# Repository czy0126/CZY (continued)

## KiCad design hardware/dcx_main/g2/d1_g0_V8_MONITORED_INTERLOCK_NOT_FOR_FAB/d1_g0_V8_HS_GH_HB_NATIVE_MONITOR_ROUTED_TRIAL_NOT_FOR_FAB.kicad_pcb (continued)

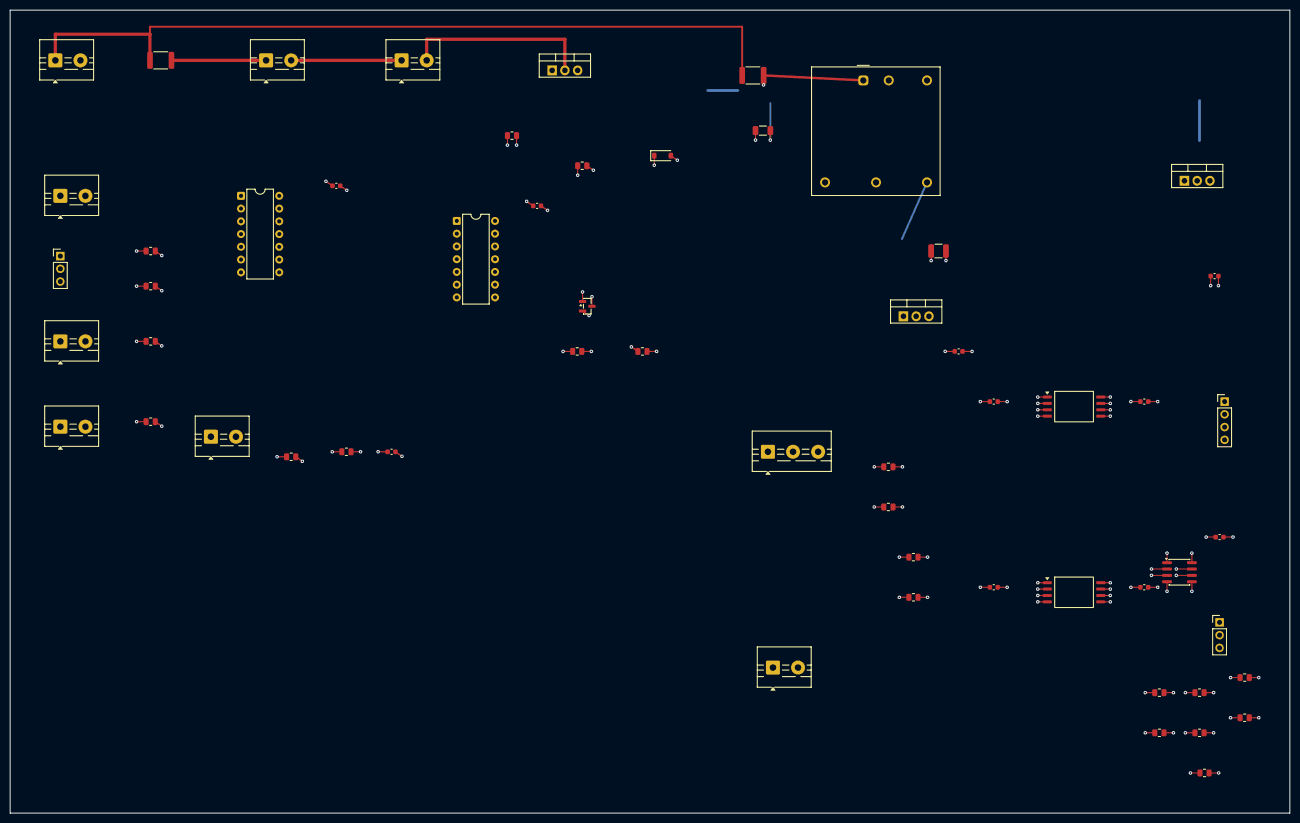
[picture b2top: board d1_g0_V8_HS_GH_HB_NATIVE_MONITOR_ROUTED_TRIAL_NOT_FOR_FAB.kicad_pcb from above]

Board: 6 copper layers, 255.0 x 160.0 mm, 58 parts (0 on the bottom side), 37 nets.

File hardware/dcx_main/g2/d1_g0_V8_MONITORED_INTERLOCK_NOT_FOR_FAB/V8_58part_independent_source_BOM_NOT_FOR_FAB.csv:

Reference,VendorOrCandidateValue,KiCadNativeFootprint,IndependentPadNetContract,NativeKiCad_DNP,AssemblyQualified,G0FabApproved
C_AND,100nF_25V,Capacitor_SMD:C_0603_1608Metric,1=VCC12;2=PGND,NO,NO,NO
C_ARM,100nF_25V_DEBOUNCE_START,Capacitor_SMD:C_0603_1608Metric,1=ARM_CLOCK;2=PGND,NO,NO,NO
C_GH_H,100nF_HS5V_LOCAL,Capacitor_SMD:C_0603_1608Metric,1=HS5V;2=HS_SW,NO,NO,NO
C_GH_L,100nF_PRI5V_LOCAL,Capacitor_SMD:C_0603_1608Metric,1=PRI5V;2=PGND,NO,NO,NO
C_HB_H,100nF_HS5V_LOCAL,Capacitor_SMD:C_0603_1608Metric,1=HS5V;2=HS_SW,NO,NO,NO
C_HB_L,100nF_PRI5V_LOCAL,Capacitor_SMD:C_0603_1608Metric,1=PRI5V;2=PGND,NO,NO,NO
C_HS5,100nF_25V_X7R,Capacitor_SMD:C_0603_1608Metric,1=HS5V;2=HS_SW,NO,NO,NO
C_HS_COMP,100nF_PRI5V_TO_PGND,Capacitor_SMD:C_0603_1608Metric,1=PRI5V;2=PGND,NO,NO,NO
C_HS_IN,1uF_100V_X7R,Capacitor_SMD:C_1206_3216Metric,1=VIN48_HS_F;2=PGND,NO,NO,NO
C_HS_OUT,22uF_25V_X7R,Capacitor_SMD:C_1210_3225Metric,1=HS_VB;2=HS_SW,NO,NO,NO
C_LATCH,100nF_25V,Capacitor_SMD:C_0603_1608Metric,1=VCC12;2=PGND,NO,NO,NO
C_PRI5,100nF_25V_X7R,Capacitor_SMD:C_0603_1608Metric,1=PRI5V;2=PGND,NO,NO,NO
D_GS,13V_ZENER_1_CATHODE_G_2_ANODE_S_DFM_REVIEW,Diode_SMD:D_SOD-123,1=MOS_GATE;2=PGND,NO,NO,NO
F_COIL,2A_SLOW_75VDC_MIN_BREAKING_I2T_UNQUALIFIED,Fuse:Fuse_1812_4532Metric,1=VIN48_AUX;2=48V_FUSED,NO,NO,NO
F_HS12,2A_SLOW_DC_BREAKING_UNQUALIFIED,Fuse:Fuse_1812_4532Metric,1=VIN48_AUX;2=VIN48_HS_F,NO,NO,NO
J_ARM,MOMENTARY_NO_MANUAL_RESTART_REQUIRED,TerminalBlock:TerminalBlock_MaiXu_MX126-5.0-02P_1x02_P5.00mm,1=VCC12;2=ARM_RAW,NO,NO,NO
J_AUX48,48V_AUX_PRE_POWER_DC_FUSED_INLET,TerminalBlock:TerminalBlock_MaiXu_MX126-5.0-02P_1x02_P5.00mm,1=VIN48_AUX;2=PGND,NO,NO,NO
J_BIAS,V6_BIAS_PRIMARY_12V_PGND,TerminalBlock:TerminalBlock_MaiXu_MX126-5.0-02P_1x02_P5.00mm,1=VCC12;2=PGND,NO,NO,NO
J_ESTOP_MON,2ND_INDEPENDENT_NC_ESTOP_CONTACT_CHANNEL_B,TerminalBlock:TerminalBlock_MaiXu_MX126-5.0-02P_1x02_P5.00mm,1=VCC12;2=ESTOP_MON_OK,NO,NO,NO
J_ESTOP_PWR,EXTERNAL_2_CONTACT_NC_ESTOP_CHANNEL_A,TerminalBlock:TerminalBlock_MaiXu_MX126-5.0-02P_1x02_P5.00mm,1=48V_FUSED;2=48V_AFTER_ESTOP,NO,NO,NO
J_GX14COIL,GX14FAC_48V_COIL_LEADS_EXTERNAL_NO_EXTRA_DIODE,TerminalBlock:TerminalBlock_MaiXu_MX126-5.0-02P_1x02_P5.00mm,1=48V_AFTER_ESTOP;2=COIL_DRAIN,NO,NO,NO
J_HEALTH,V6_UVLO_P_OK_S_OK_GND,Connector_PinHeader_2.54mm:PinHeader_1x03_P2.54mm_Vertical,1=UVLO_P_OK;2=UVLO_S_PRIMARY_OK;3=PGND,NO,NO,NO
J_HS_DIFF,GH_OUTP_GH_OUTN_HB_OUTP_HB_OUTN,Connector_PinHeader_2.54mm:PinHeader_1x04_P2.54mm_Vertical,1=GH_OUTP;2=GH_OUTN;3=HB_OUTP;4=HB_OUTN,NO,NO,NO
J_HS_FLAGS,HB_VALID_GH_OFF_PGND_DIAGNOSTICS_ONLY,Connector_PinHeader_2.54mm:PinHeader_1x03_P2.54mm_Vertical,1=HB_VALID;2=GH_GATE_OFF;3=PGND,NO,NO,NO
J_HS_FLOAT_BIAS,FLOATING_12V_HB_AND_SW_TO_DRIVER_CHECK_V5_COMPATIBILITY,TerminalBlock:TerminalBlock_MaiXu_MX126-5.0-02P_1x02_P5.00mm,1=HS_VB;2=HS_SW,NO,NO,NO
J_HS_OK,INDEPENDENT_HS_GH_SW_SENSOR_OK_MANDATORY,TerminalBlock:TerminalBlock_MaiXu_MX126-5.0-02P_1x02_P5.00mm,1=HS_OK_IN;2=PGND,NO,NO,NO
J_HS_SENSE,HIGH_SIDE_GH1_HB_AND_KELVIN_SW_FROM_ACTUAL_DRIVER,TerminalBlock:TerminalBlock_MaiXu_MX126-5.0-03P_1x03_P5.00mm,1=GH_RAW;2=HB_RAW;3=HS_SW,NO,NO,NO
Q_COIL,Infineon_IRL540NPbF_100V_36A_G1D2S3,Package_TO_SOT_THT:TO-220-3_Vertical,1=MOS_GATE;2=COIL_DRAIN;3=PGND,NO,NO,NO
Q_RESET,onsemi_MMBT3904LT1G_1B_2E_3C,Package_TO_SOT_SMD:SOT-23,1=RESET_BASE;2=PGND;3=RESET_ACTIVE,NO,NO,NO
R_ARM_DN,100k_0805_FAIL_OFF,Resistor_SMD:R_0805_2012Metric,1=ARM_RAW;2=PGND,NO,NO,NO
R_ARM_SER,4k7_0805,Resistor_SMD:R_0805_2012Metric,1=ARM_RAW;2=ARM_CLOCK,NO,NO,NO
R_ESTOP_DN,100k_0805_FAIL_OFF,Resistor_SMD:R_0805_2012Metric,1=ESTOP_MON_OK;2=PGND,NO,NO,NO
R_GATE,100R_0805,Resistor_SMD:R_0805_2012Metric,1=COIL_ENABLE;2=MOS_GATE,NO,NO,NO
R_GATE_OFF,100k_0805_GS_PULLDOWN,Resistor_SMD:R_0805_2012Metric,1=MOS_GATE;2=PGND,NO,NO,NO
R_GH_BOT,10k_1pct_GH_DIVIDER,Resistor_SMD:R_0805_2012Metric,1=GH_DIV;2=HS_SW,NO,NO,NO
R_GH_PULL,4k7_0805_GH_OFF_PRI5V_PULL,Resistor_SMD:R_0805_2012Metric,1=PRI5V;2=GH_GATE_OFF,NO,NO,NO
R_GH_RBOT,10k_0805_REF_GH,Resistor_SMD:R_0805_2012Metric,1=GH_REF;2=PGND,NO,NO,NO
R_GH_RTOP,22k_0805_REF_GH,Resistor_SMD:R_0805_2012Metric,1=PRI5V;2=GH_REF,NO,NO,NO
R_GH_TOP,100k_1pct_GH_DIVIDER,Resistor_SMD:R_0805_2012Metric,1=GH_RAW;2=GH_DIV,NO,NO,NO
R_HB_BOT,10k_1pct_HB_DIVIDER,Resistor_SMD:R_0805_2012Metric,1=HB_DIV;2=HS_SW,NO,NO,NO
R_HB_PULL,4k7_0805_HB_VALID_PRI5V_PULL,Resistor_SMD:R_0805_2012Metric,1=PRI5V;2=HB_VALID,NO,NO,NO
R_HB_RBOT,10k_0805_REF_HB,Resistor_SMD:R_0805_2012Metric,1=HB_REF;2=PGND,NO,NO,NO
R_HB_RTOP,16k_0805_REF_HB_1pct,Resistor_SMD:R_0805_2012Metric,1=PRI5V;2=HB_REF,NO,NO,NO
R_HB_TOP,100k_1pct_HB_DIVIDER,Resistor_SMD:R_0805_2012Metric,1=HB_RAW;2=HB_DIV,NO,NO,NO
R_HS_DN,100k_0805_FAIL_OFF,Resistor_SMD:R_0805_2012Metric,1=HS_OK_IN;2=PGND,NO,NO,NO
R_HS_RELEASE,0R_DNP_ALWAYS_NO_AUTO_ENABLE_OR_SELF_TEST_BYPASS,Resistor_SMD:R_0805_2012Metric,1=HB_VALID;2=HS_OK_IN,YES,NO,NO
R_P_DN,100k_0805_FAIL_OFF,Resistor_SMD:R_0805_2012Metric,1=UVLO_P_OK;2=PGND,NO,NO,NO
R_RESET_B,47k_0805_1pct,Resistor_SMD:R_0805_2012Metric,1=ALL_HEALTHY;2=RESET_BASE,NO,NO,NO
R_RESET_PULL,10k_0805_1pct,Resistor_SMD:R_0805_2012Metric,1=VCC12;2=RESET_ACTIVE,NO,NO,NO
R_S_DN,100k_0805_FAIL_OFF,Resistor_SMD:R_0805_2012Metric,1=UVLO_S_PRIMARY_OK;2=PGND,NO,NO,NO
U_AND,TI_CD4081BE_QUAD_2IN_AND,Package_DIP:DIP-14_W7.62mm,1=UVLO_P_OK;2=UVLO_S_PRIMARY_OK;3=BIAS_BOTH_OK;4=EXT_BOTH_OK;5=HS_OK_IN;6=ESTOP_MON_OK;7=PGND;8=BIAS_BOTH_OK;9=EXT_BOTH_OK;10=ALL_HEALTHY;11=COIL_ENABLE;12=LATCH_Q;13=ALL_HEALTHY;14=VCC12,NO,NO,NO
U_GH_SENSE,TI_AMC1311BDWVR_REINFORCED_ISOLATION_GH_MINUS_SW,Package_SO:SOIC-8_7.5x5.85mm_P1.27mm,1=HS5V;2=GH_DIV;3=HS_SW;4=HS_SW;5=PGND;6=GH_OUTN;7=GH_OUTP;8=PRI5V,NO,NO,NO
U_HB_SENSE,TI_AMC1311BDWVR_REINFORCED_ISOLATION_HB_MINUS_SW,Package_SO:SOIC-8_7.5x5.85mm_P1.27mm,1=HS5V;2=HB_DIV;3=HS_SW;4=HS_SW;5=PGND;6=HB_OUTN;7=HB_OUTP;8=PRI5V,NO,NO,NO
U_HS12,Traco_THN_30-4812_FLOATING_12V_HS_36-75V,Converter_DCDC:Converter_DCDC_TRACO_THN30-xxxx_THT,1=VIN48_HS_F;2=PGND;3=HS_VB;4=;5=HS_SW;6=,NO,NO,NO
U_HS_COMP,TI_LM393BIDR_DIAGNOSTIC_ONLY,Package_SO:SOIC-8_3.9x4.9mm_P1.27mm,1=HB_VALID;2=HB_REF;3=HB_OUTP;4=PGND;5=GH_REF;6=GH_OUTP;7=GH_GATE_OFF;8=PRI5V,NO,NO,NO
U_LATCH,TI_CD4013BE_DUAL_D_FF_ACTIVE_HIGH_ASYNC_RESET,Package_DIP:DIP-14_W7.62mm,1=LATCH_Q;2=;3=ARM_CLOCK;4=RESET_ACTIVE;5=VCC12;6=PGND;7=PGND;8=PGND;9=PGND;10=PGND;11=PGND;12=;13=;14=VCC12,NO,NO,NO
U_LDO_HS,ON_MC7805CTG_FLOATING_5V,Package_TO_SOT_THT:TO-220-3_Vertical,1=HS_VB;2=HS_SW;3=HS5V,NO,NO,NO
U_LDO_P,ON_MC7805CTG_PRIMARY_5V,Package_TO_SOT_THT:TO-220-3_Vertical,1=VCC12;2=PGND;3=PRI5V,NO,NO,NO
